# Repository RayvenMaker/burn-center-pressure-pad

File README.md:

# burn-center-pressure-pad
A 128 x 128 pressure sensing matrix designed to work in a hospital setting.

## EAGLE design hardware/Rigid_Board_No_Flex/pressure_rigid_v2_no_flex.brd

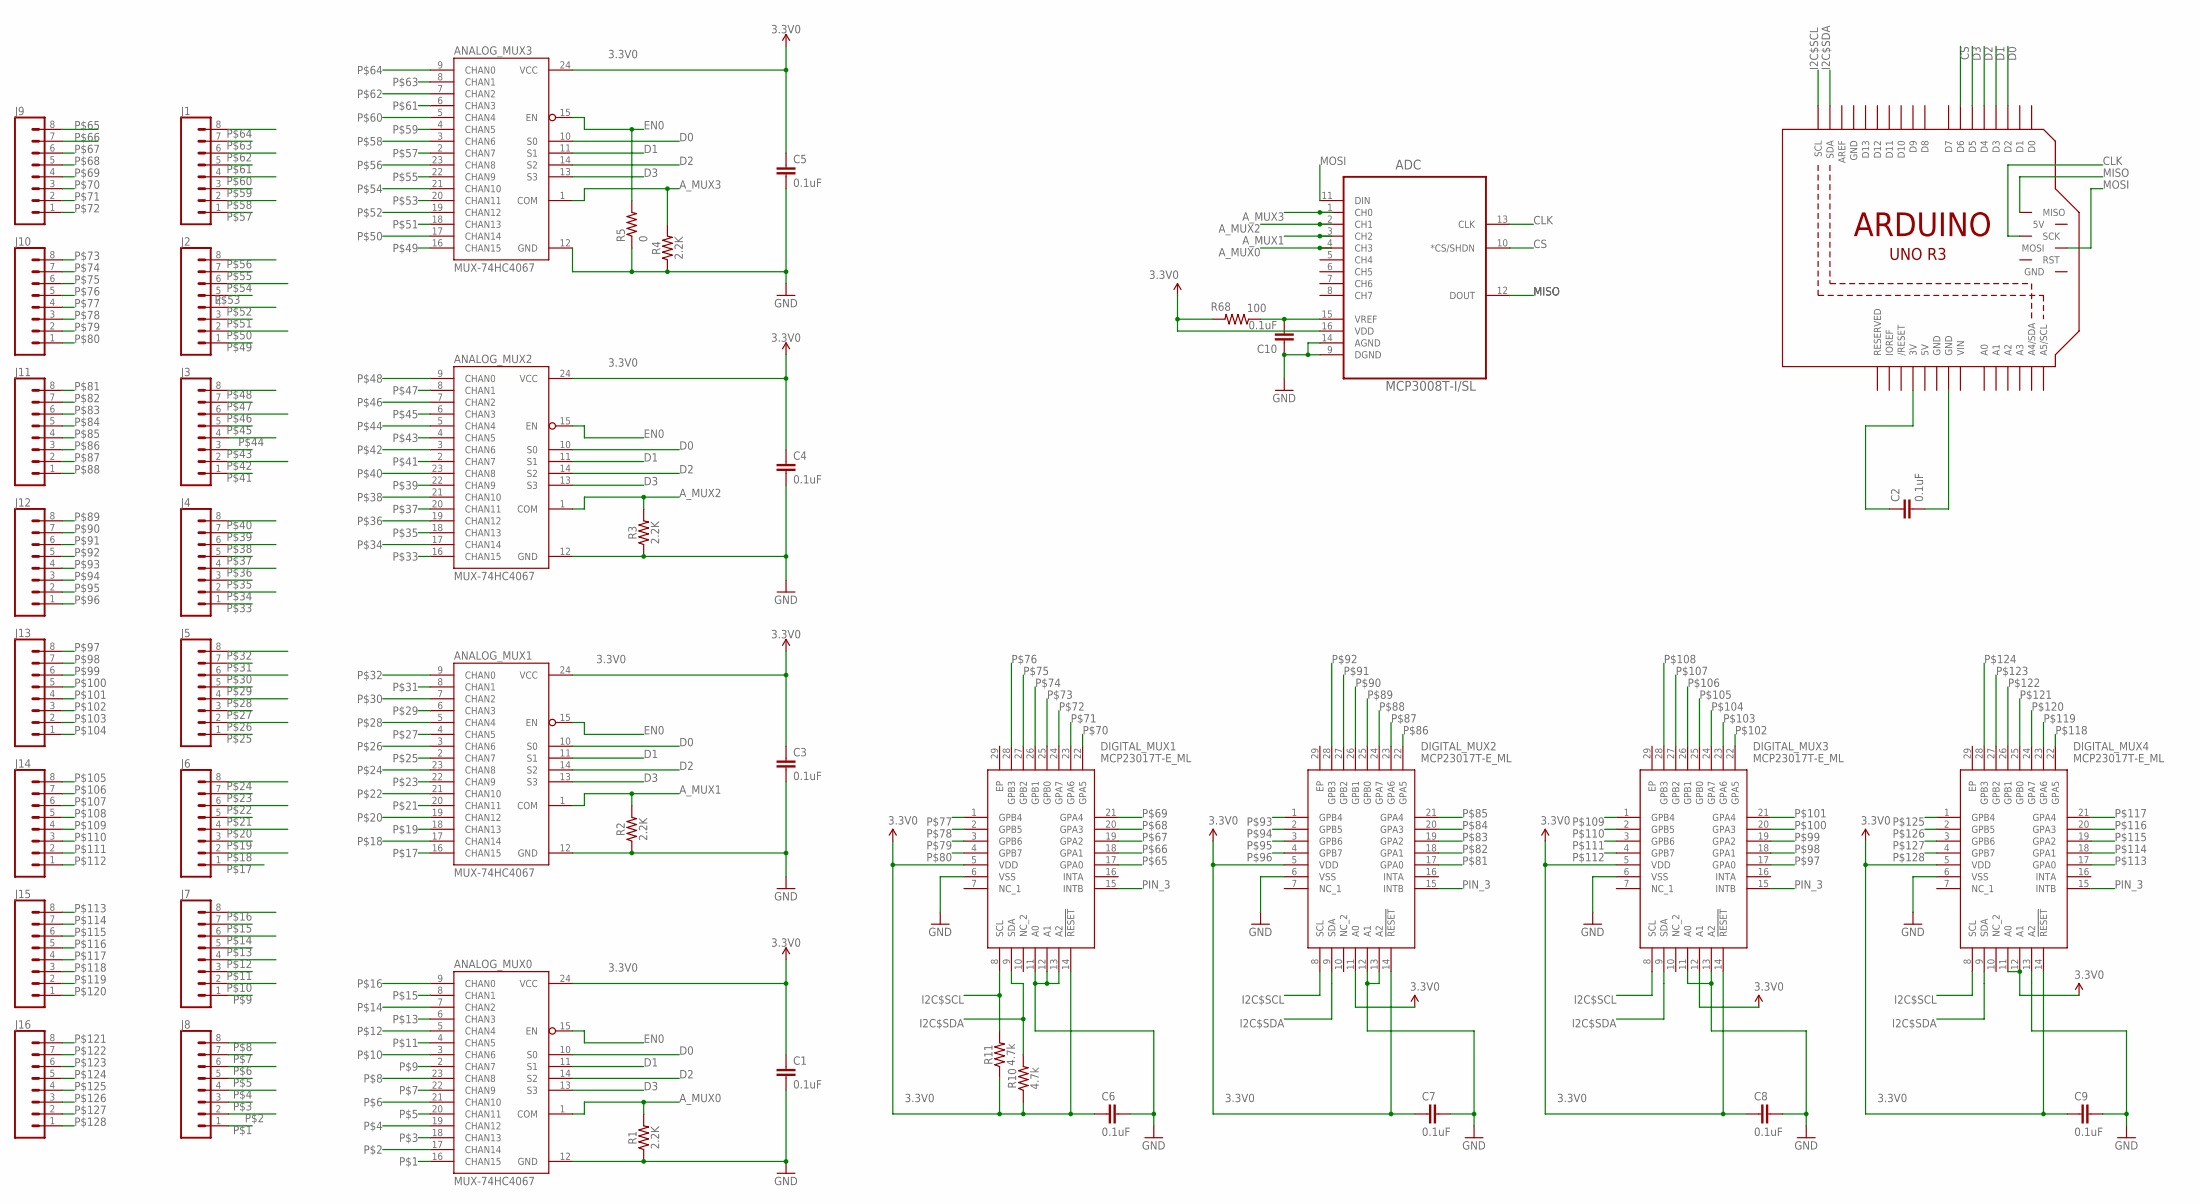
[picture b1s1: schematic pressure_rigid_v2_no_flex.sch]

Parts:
ADC: MCP3008T-I/SL; SOIC127P600X175-16N
ANALOG_MUX0, ANALOG_MUX1, ANALOG_MUX2, ANALOG_MUX3: MUX-74HC4067; SSOP24
C1, C3, C4, C5, C6, C7, C8, C9, C10: 0.1uF; 0402
C2: 0.1uF; 0603
DIGITAL_MUX1, DIGITAL_MUX2, DIGITAL_MUX3, DIGITAL_MUX4: MCP23017T-E_ML; QFN65P600X600X100-29N
J1, J2, J3, J4, J5, J6, J7, J8, J9, J10, J11, J12, J13, J14, J15, J16: CONN_08SMD-STRAIGHT-FEMALE; 1X08_SMD
M1: ARDUINO_R3_ICSP_NODIM; ARDUINOR3_ICSP_NODIM
R1, R2, R3, R4: 2.2K; 0402
R5: 0; 0603
R10, R11: 4.7k; 0603
R68: 100; 0603

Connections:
3.3V0: ANALOG_MUX0.24 (VCC), ANALOG_MUX1.24 (VCC), ANALOG_MUX2.24 (VCC), ANALOG_MUX3.24 (VCC), C1.1, C3.1, C4.1, C5.1, C6.1, C7.1, C8.1, C9.1, DIGITAL_MUX1.5 (VDD), DIGITAL_MUX1.14 (!RESET), DIGITAL_MUX2.5 (VDD), DIGITAL_MUX2.14 (!RESET), DIGITAL_MUX3.5 (VDD), DIGITAL_MUX3.14 (!RESET), DIGITAL_MUX4.5 (VDD), DIGITAL_MUX4.14 (!RESET), R10.1, R11.1
5V: M1.5V
A_MUX0: ADC.4 (CH3), ANALOG_MUX0.1 (COM), R1.2
A_MUX1: ADC.3 (CH2), ANALOG_MUX1.1 (COM), R2.2
A_MUX2: ADC.2 (CH1), ANALOG_MUX2.1 (COM), R3.2
A_MUX3: ADC.1 (CH0), ANALOG_MUX3.1 (COM), R4.2
CLK: ADC.13 (CLK), M1.SCK
CS: ADC.10 (*CS/SHDN), M1.D6
D0: ANALOG_MUX0.10 (S0), ANALOG_MUX1.10 (S0), ANALOG_MUX2.10 (S0), ANALOG_MUX3.10 (S0), M1.D2
D1: ANALOG_MUX0.11 (S1), ANALOG_MUX1.11 (S1), ANALOG_MUX2.11 (S1), ANALOG_MUX3.11 (S1), M1.D3
D2: ANALOG_MUX0.14 (S2), ANALOG_MUX1.14 (S2), ANALOG_MUX2.14 (S2), ANALOG_MUX3.14 (S2), M1.D4
D3: ANALOG_MUX0.13 (S3), ANALOG_MUX1.13 (S3), ANALOG_MUX2.13 (S3), ANALOG_MUX3.13 (S3), M1.D5
EN0: ANALOG_MUX0.15 (EN), ANALOG_MUX1.15 (EN), ANALOG_MUX2.15 (EN), ANALOG_MUX3.15 (EN), R5.2
GND: ADC.9 (DGND), ADC.14 (AGND), ANALOG_MUX0.12 (GND), ANALOG_MUX1.12 (GND), ANALOG_MUX2.12 (GND), ANALOG_MUX3.12 (GND), C1.2, C3.2, C4.2, C5.2, C6.2, C7.2, C8.2, C9.2, C10.1, DIGITAL_MUX1.6 (VSS), DIGITAL_MUX1.11 (A0), DIGITAL_MUX1.12 (A1), DIGITAL_MUX1.13 (A2), DIGITAL_MUX2.6 (VSS), DIGITAL_MUX2.12 (A1), DIGITAL_MUX2.13 (A2), DIGITAL_MUX3.6 (VSS), DIGITAL_MUX3.11 (A0), DIGITAL_MUX3.13 (A2), DIGITAL_MUX4.6 (VSS), DIGITAL_MUX4.13 (A2), M1.GND, M1.GND@1 (GND), R1.1, R2.1, R3.1, R4.1, R5.1
I2C$SCL: DIGITAL_MUX1.8 (SCL), DIGITAL_MUX2.8 (SCL), DIGITAL_MUX3.8 (SCL), DIGITAL_MUX4.8 (SCL), M1.SCL, R11.2
I2C$SDA: DIGITAL_MUX1.9 (SDA), DIGITAL_MUX2.9 (SDA), DIGITAL_MUX3.9 (SDA), DIGITAL_MUX4.9 (SDA), M1.SDA, R10.2
MISO: ADC.12 (DOUT), M1.MISO
MOSI: ADC.11 (DIN), M1.MOSI
unnamed: ADC.15 (VREF), C10.2, R68.1
unnamed: C2.2, M1.GND@3 (GND)
unnamed: C2.1, M1.3V
P$1: ANALOG_MUX0.16 (CHAN15), J8.1
P$2: ANALOG_MUX0.17 (CHAN14), J8.2
P$3: ANALOG_MUX0.18 (CHAN13), J8.3
P$4: ANALOG_MUX0.19 (CHAN12), J8.4
P$5: ANALOG_MUX0.20 (CHAN11), J8.5
P$6: ANALOG_MUX0.21 (CHAN10), J8.6
P$7: ANALOG_MUX0.22 (CHAN9), J8.7
P$8: ANALOG_MUX0.23 (CHAN8), J8.8
P$9: ANALOG_MUX0.2 (CHAN7), J7.1
P$10: ANALOG_MUX0.3 (CHAN6), J7.2
P$11: ANALOG_MUX0.4 (CHAN5), J7.3
P$12: ANALOG_MUX0.5 (CHAN4), J7.4
P$13: ANALOG_MUX0.6 (CHAN3), J7.5
P$14: ANALOG_MUX0.7 (CHAN2), J7.6
P$15: ANALOG_MUX0.8 (CHAN1), J7.7
P$16: ANALOG_MUX0.9 (CHAN0), J7.8
P$17: ANALOG_MUX1.16 (CHAN15), J6.1
P$18: ANALOG_MUX1.17 (CHAN14), J6.2
P$19: ANALOG_MUX1.18 (CHAN13), J6.3
P$20: ANALOG_MUX1.19 (CHAN12), J6.4
P$21: ANALOG_MUX1.20 (CHAN11), J6.5
P$22: ANALOG_MUX1.21 (CHAN10), J6.6
P$23: ANALOG_MUX1.22 (CHAN9), J6.7
P$24: ANALOG_MUX1.23 (CHAN8), J6.8
P$25: ANALOG_MUX1.2 (CHAN7), J5.1
P$26: ANALOG_MUX1.3 (CHAN6), J5.2
P$27: ANALOG_MUX1.4 (CHAN5), J5.3
P$28: ANALOG_MUX1.5 (CHAN4), J5.4
P$29: ANALOG_MUX1.6 (CHAN3), J5.5
P$30: ANALOG_MUX1.7 (CHAN2), J5.6
P$31: ANALOG_MUX1.8 (CHAN1), J5.7
P$32: ANALOG_MUX1.9 (CHAN0), J5.8
P$33: ANALOG_MUX2.16 (CHAN15), J4.1
P$34: ANALOG_MUX2.17 (CHAN14), J4.2
P$35: ANALOG_MUX2.18 (CHAN13), J4.3
P$36: ANALOG_MUX2.19 (CHAN12), J4.4
P$37: ANALOG_MUX2.20 (CHAN11), J4.5
P$38: ANALOG_MUX2.21 (CHAN10), J4.6
P$39: ANALOG_MUX2.22 (CHAN9), J4.7
P$40: ANALOG_MUX2.23 (CHAN8), J4.8
P$41: ANALOG_MUX2.2 (CHAN7), J3.1
P$42: ANALOG_MUX2.3 (CHAN6), J3.2
P$43: ANALOG_MUX2.4 (CHAN5), J3.3
P$44: ANALOG_MUX2.5 (CHAN4), J3.4
P$45: ANALOG_MUX2.6 (CHAN3), J3.5
P$46: ANALOG_MUX2.7 (CHAN2), J3.6
P$47: ANALOG_MUX2.8 (CHAN1), J3.7
P$48: ANALOG_MUX2.9 (CHAN0), J3.8
P$49: ANALOG_MUX3.16 (CHAN15), J2.1
P$50: ANALOG_MUX3.17 (CHAN14), J2.2
P$51: ANALOG_MUX3.18 (CHAN13), J2.3
P$52: ANALOG_MUX3.19 (CHAN12), J2.4
P$53: ANALOG_MUX3.20 (CHAN11), J2.5
P$54: ANALOG_MUX3.21 (CHAN10), J2.6
P$55: ANALOG_MUX3.22 (CHAN9), J2.7
P$56: ANALOG_MUX3.23 (CHAN8), J2.8
P$57: ANALOG_MUX3.2 (CHAN7), J1.1
P$58: ANALOG_MUX3.3 (CHAN6), J1.2
P$59: ANALOG_MUX3.4 (CHAN5), J1.3
P$60: ANALOG_MUX3.5 (CHAN4), J1.4
P$61: ANALOG_MUX3.6 (CHAN3), J1.5
P$62: ANALOG_MUX3.7 (CHAN2), J1.6
P$63: ANALOG_MUX3.8 (CHAN1), J1.7
P$64: ANALOG_MUX3.9 (CHAN0), J1.8
P$65: DIGITAL_MUX1.17 (GPA0), J9.8
P$66: DIGITAL_MUX1.18 (GPA1), J9.7
P$67: DIGITAL_MUX1.19 (GPA2), J9.6
P$68: DIGITAL_MUX1.20 (GPA3), J9.5
P$69: DIGITAL_MUX1.21 (GPA4), J9.4
P$70: DIGITAL_MUX1.22 (GPA5), J9.3
P$71: DIGITAL_MUX1.23 (GPA6), J9.2
P$72: DIGITAL_MUX1.24 (GPA7), J9.1
P$73: DIGITAL_MUX1.25 (GPB0), J10.8
P$74: DIGITAL_MUX1.26 (GPB1), J10.7
P$75: DIGITAL_MUX1.27 (GPB2), J10.6
P$76: DIGITAL_MUX1.28 (GPB3), J10.5
P$77: DIGITAL_MUX1.1 (GPB4), J10.4
P$78: DIGITAL_MUX1.2 (GPB5), J10.3
P$79: DIGITAL_MUX1.3 (GPB6), J10.2
P$80: DIGITAL_MUX1.4 (GPB7), J10.1
P$81: DIGITAL_MUX2.17 (GPA0), J11.8
P$82: DIGITAL_MUX2.18 (GPA1), J11.7
P$83: DIGITAL_MUX2.19 (GPA2), J11.6
P$84: DIGITAL_MUX2.20 (GPA3), J11.5
P$85: DIGITAL_MUX2.21 (GPA4), J11.4
P$86: DIGITAL_MUX2.22 (GPA5), J11.3
P$87: DIGITAL_MUX2.23 (GPA6), J11.2
P$88: DIGITAL_MUX2.24 (GPA7), J11.1
P$89: DIGITAL_MUX2.25 (GPB0), J12.8
P$90: DIGITAL_MUX2.26 (GPB1), J12.7
P$91: DIGITAL_MUX2.27 (GPB2), J12.6
P$92: DIGITAL_MUX2.28 (GPB3), J12.5
P$93: DIGITAL_MUX2.1 (GPB4), J12.4
P$94: DIGITAL_MUX2.2 (GPB5), J12.3
P$95: DIGITAL_MUX2.3 (GPB6), J12.2
P$96: DIGITAL_MUX2.4 (GPB7), J12.1
P$97: DIGITAL_MUX3.17 (GPA0), J13.8
P$98: DIGITAL_MUX3.18 (GPA1), J13.7
P$99: DIGITAL_MUX3.19 (GPA2), J13.6
P$100: DIGITAL_MUX3.20 (GPA3), J13.5
P$101: DIGITAL_MUX3.21 (GPA4), J13.4
P$102: DIGITAL_MUX3.22 (GPA5), J13.3
P$103: DIGITAL_MUX3.23 (GPA6), J13.2
P$104: DIGITAL_MUX3.24 (GPA7), J13.1
P$105: DIGITAL_MUX3.25 (GPB0), J14.8
P$106: DIGITAL_MUX3.26 (GPB1), J14.7
P$107: DIGITAL_MUX3.27 (GPB2), J14.6
P$108: DIGITAL_MUX3.28 (GPB3), J14.5
P$109: DIGITAL_MUX3.1 (GPB4), J14.4
P$110: DIGITAL_MUX3.2 (GPB5), J14.3
P$111: DIGITAL_MUX3.3 (GPB6), J14.2
P$112: DIGITAL_MUX3.4 (GPB7), J14.1
P$113: DIGITAL_MUX4.17 (GPA0), J15.8
P$114: DIGITAL_MUX4.18 (GPA1), J15.7
P$115: DIGITAL_MUX4.19 (GPA2), J15.6
P$116: DIGITAL_MUX4.20 (GPA3), J15.5
P$117: DIGITAL_MUX4.21 (GPA4), J15.4
P$118: DIGITAL_MUX4.22 (GPA5), J15.3
P$119: DIGITAL_MUX4.23 (GPA6), J15.2
P$120: DIGITAL_MUX4.24 (GPA7), J15.1
P$121: DIGITAL_MUX4.25 (GPB0), J16.8
P$122: DIGITAL_MUX4.26 (GPB1), J16.7
P$123: DIGITAL_MUX4.27 (GPB2), J16.6
P$124: DIGITAL_MUX4.28 (GPB3), J16.5
P$125: DIGITAL_MUX4.1 (GPB4), J16.4
P$126: DIGITAL_MUX4.2 (GPB5), J16.3
P$127: DIGITAL_MUX4.3 (GPB6), J16.2
P$128: DIGITAL_MUX4.4 (GPB7), J16.1
PIN_3: DIGITAL_MUX1.15 (INTB), DIGITAL_MUX2.15 (INTB), DIGITAL_MUX3.15 (INTB), DIGITAL_MUX4.15 (INTB)
VCC: ADC.16 (VDD), DIGITAL_MUX2.11 (A0), DIGITAL_MUX3.12 (A1), DIGITAL_MUX4.11 (A0), DIGITAL_MUX4.12 (A1), R68.2
VIN: M1.VIN

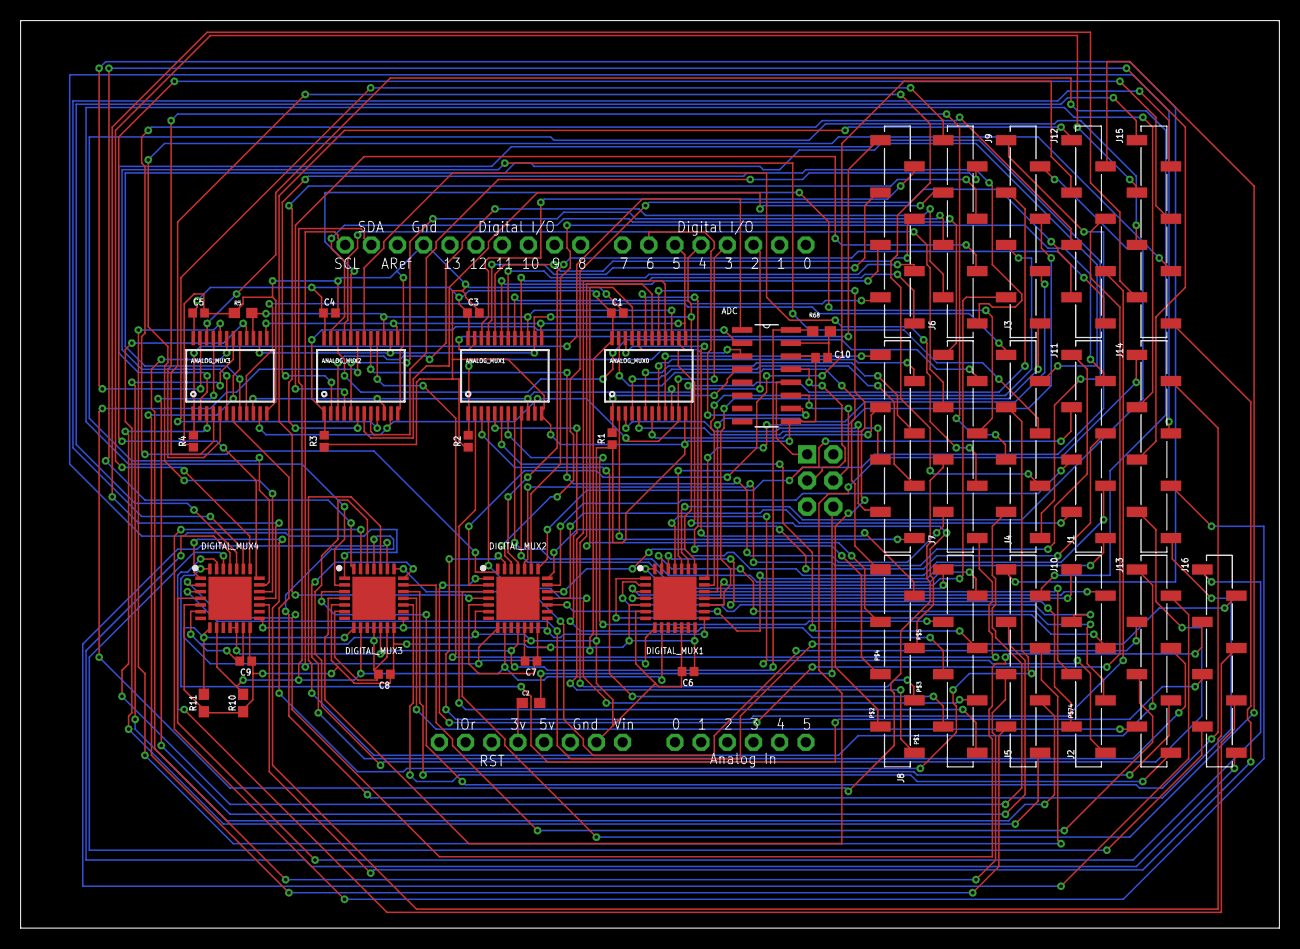
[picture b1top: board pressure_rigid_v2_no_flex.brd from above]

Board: 2 copper layers, 122.2 x 88.1 mm, 44 parts (0 on the bottom side), 150 nets.

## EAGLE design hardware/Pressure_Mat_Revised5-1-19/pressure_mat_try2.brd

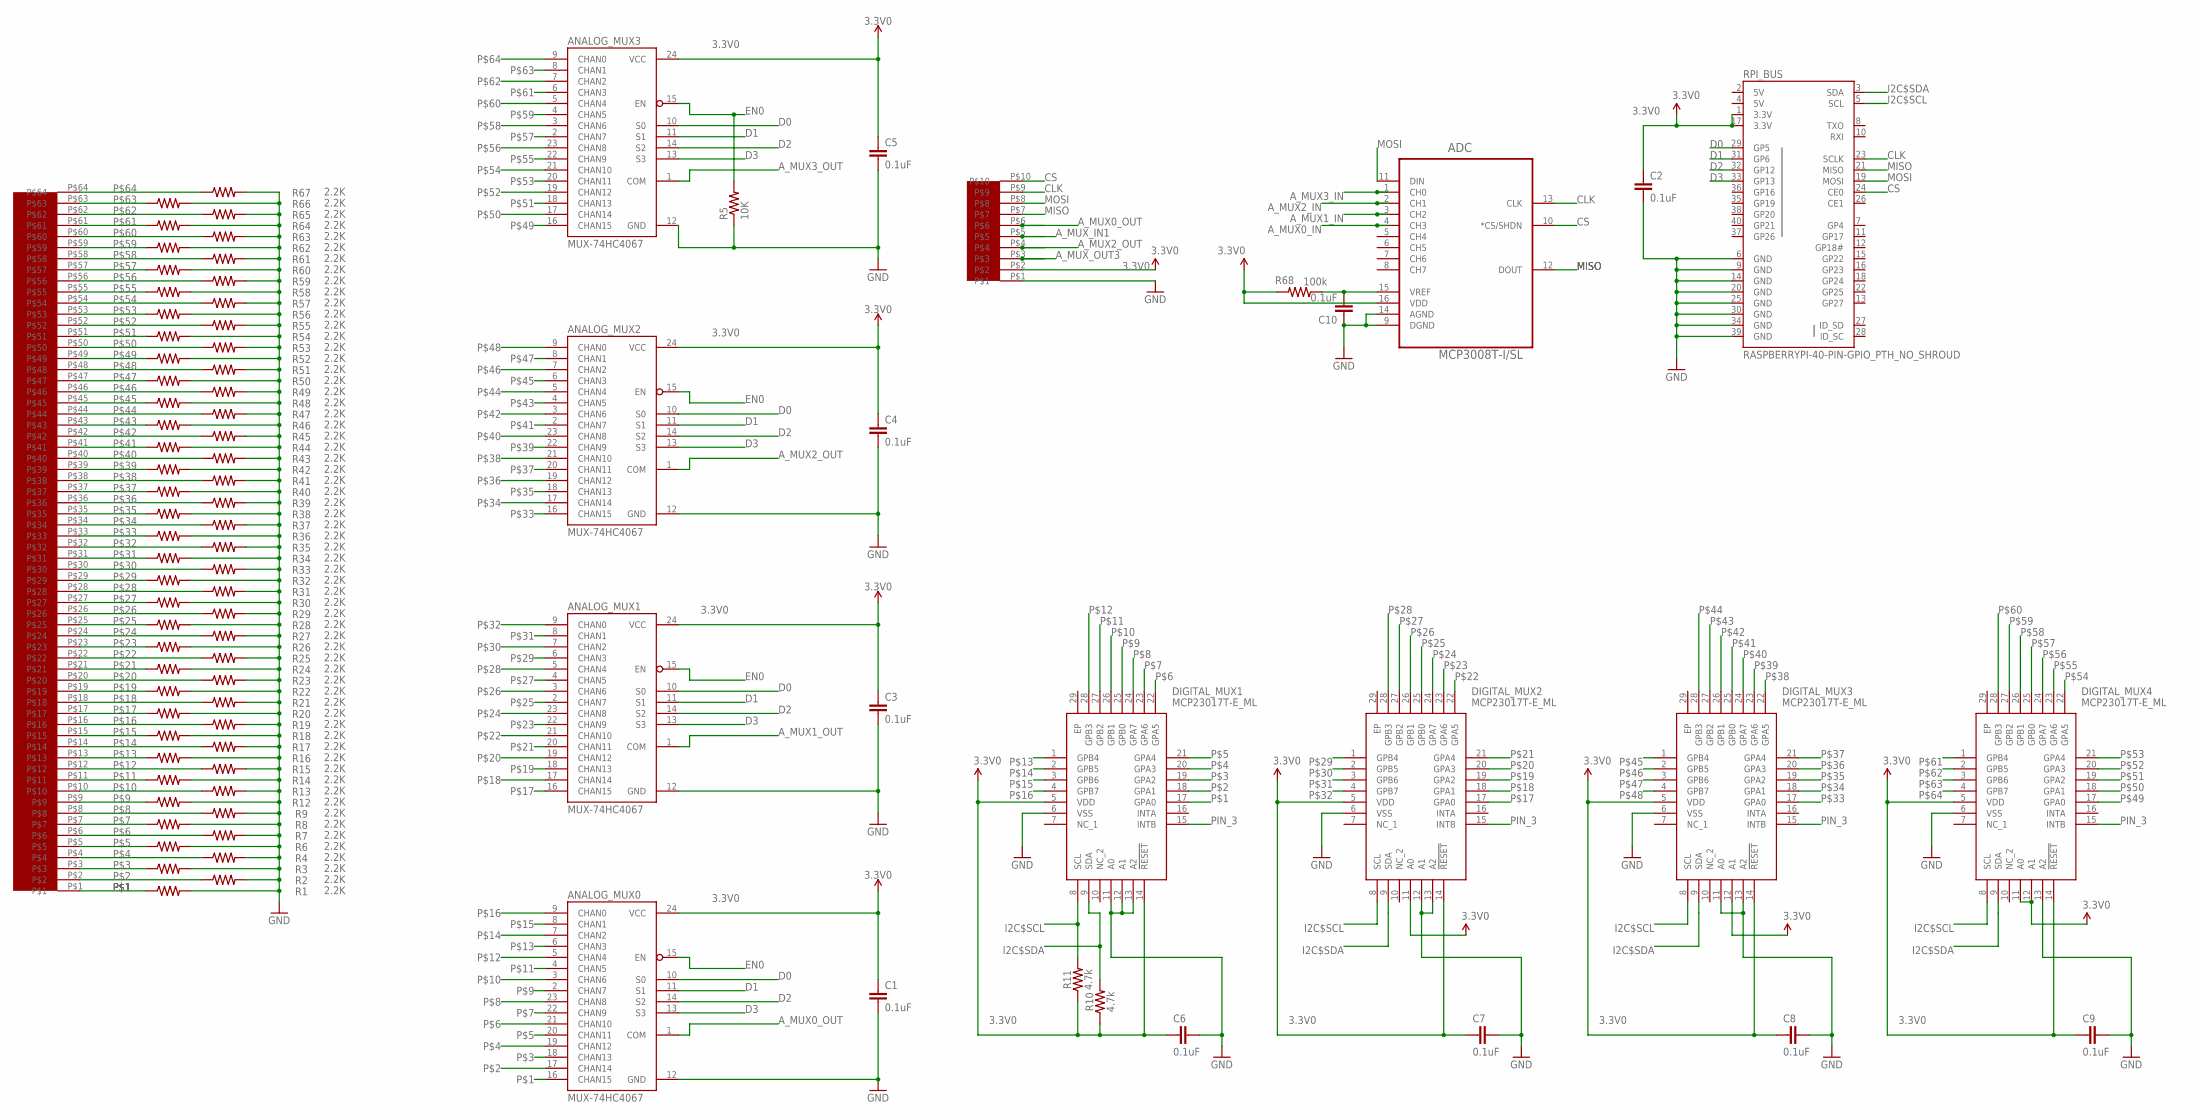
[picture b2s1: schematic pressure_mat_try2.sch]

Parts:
ADC: MCP3008T-I/SL; SOIC127P600X175-16N
ANALOG_MUX0, ANALOG_MUX1, ANALOG_MUX2, ANALOG_MUX3: MUX-74HC4067; SSOP24
C1, C3, C4, C5, C6, C7, C8, C9, C10: 0.1uF; 0402
C2: 0.1uF; 0603
DIGITAL_MUX1, DIGITAL_MUX2, DIGITAL_MUX3, DIGITAL_MUX4: MCP23017T-E_ML; QFN65P600X600X100-29N
PAD_BUS: PCB_CONNECTOR_10_PIN
R1, R2, R3, R4, R6, R7, R8, R9, R12, R13, R14, R15, R16, R17, R18, R19, R20, R21, R22, R23, R24, R25, R26, R27, R28, R29, R30, R31, R32, R33, R34, R35, R36, R37, R38, R39, R40, R41, R42, R43, R44, R45, R46, R47, R48, R49, R50, R51, R52, R53, R54, R55, R56, R57, R58, R59, R60, R61, R62, R63, R64, R65, R66, R67: 2.2K; 0402
R5: 10K; 0603
R10, R11: 4.7k; 0603
R68: 100k; 0603
RPI_BUS: RASPBERRYPI-40-PIN-GPIO_PTH_NO_SHROUD; 2X20
U$1: 64GRID

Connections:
3.3V0: ANALOG_MUX0.24 (VCC), ANALOG_MUX1.24 (VCC), ANALOG_MUX2.24 (VCC), ANALOG_MUX3.24 (VCC), C1.1, C2.1, C3.1, C4.1, C5.1, C6.1, C7.1, C8.1, C9.1, DIGITAL_MUX1.5 (VDD), DIGITAL_MUX1.14 (!RESET), DIGITAL_MUX2.5 (VDD), DIGITAL_MUX2.14 (!RESET), DIGITAL_MUX3.5 (VDD), DIGITAL_MUX3.14 (!RESET), DIGITAL_MUX4.5 (VDD), DIGITAL_MUX4.14 (!RESET), PAD_BUS.P$2, R10.1, R11.1, RPI_BUS.1 (3.3V), RPI_BUS.17 (3.3V)
5V: RPI_BUS.2 (5V), RPI_BUS.4 (5V)
A_MUX0_IN: ADC.4 (CH3)
A_MUX0_OUT: ANALOG_MUX0.1 (COM), PAD_BUS.P$6
A_MUX1_IN: ADC.3 (CH2)
A_MUX1_OUT: ANALOG_MUX1.1 (COM)
A_MUX2_IN: ADC.2 (CH1)
A_MUX2_OUT: ANALOG_MUX2.1 (COM), PAD_BUS.P$4
A_MUX3_IN: ADC.1 (CH0)
A_MUX3_OUT: ANALOG_MUX3.1 (COM)
A_MUX_IN1: PAD_BUS.P$5
A_MUX_OUT3: PAD_BUS.P$3
CLK: ADC.13 (CLK), PAD_BUS.P$9, RPI_BUS.23 (SCLK)
CS: ADC.10 (*CS/SHDN), PAD_BUS.P$10, RPI_BUS.24 (CE0)
D0: ANALOG_MUX0.10 (S0), ANALOG_MUX1.10 (S0), ANALOG_MUX2.10 (S0), ANALOG_MUX3.10 (S0), RPI_BUS.29 (GP5)
D1: ANALOG_MUX0.11 (S1), ANALOG_MUX1.11 (S1), ANALOG_MUX2.11 (S1), ANALOG_MUX3.11 (S1), RPI_BUS.31 (GP6)
D2: ANALOG_MUX0.14 (S2), ANALOG_MUX1.14 (S2), ANALOG_MUX2.14 (S2), ANALOG_MUX3.14 (S2), RPI_BUS.32 (GP12)
D3: ANALOG_MUX0.13 (S3), ANALOG_MUX1.13 (S3), ANALOG_MUX2.13 (S3), ANALOG_MUX3.13 (S3), RPI_BUS.33 (GP13)
EN0: ANALOG_MUX0.15 (EN), ANALOG_MUX1.15 (EN), ANALOG_MUX2.15 (EN), ANALOG_MUX3.15 (EN), R5.2
GND: ADC.9 (DGND), ADC.14 (AGND), ANALOG_MUX0.12 (GND), ANALOG_MUX1.12 (GND), ANALOG_MUX2.12 (GND), ANALOG_MUX3.12 (GND), C1.2, C2.2, C3.2, C4.2, C5.2, C6.2, C7.2, C8.2, C9.2, C10.1, DIGITAL_MUX1.6 (VSS), DIGITAL_MUX1.11 (A0), DIGITAL_MUX1.12 (A1), DIGITAL_MUX1.13 (A2), DIGITAL_MUX2.6 (VSS), DIGITAL_MUX2.12 (A1), DIGITAL_MUX2.13 (A2), DIGITAL_MUX3.6 (VSS), DIGITAL_MUX3.11 (A0), DIGITAL_MUX3.13 (A2), DIGITAL_MUX4.6 (VSS), DIGITAL_MUX4.13 (A2), PAD_BUS.P$1, R1.2, R2.2, R3.2, R4.2, R5.1, R6.2, R7.2, R8.2, R9.2, R12.2, R13.2, R14.2, R15.2, R16.2, R17.2, R18.2, R19.2, R20.2, R21.2, R22.2, R23.2, R24.2, R25.2, R26.2, R27.2, R28.2, R29.2, R30.2, R31.2, R32.2, R33.2, R34.2, R35.2, R36.2, R37.2, R38.2, R39.2, R40.2, R41.2, R42.2, R43.2, R44.2, R45.2, R46.2, R47.2, R48.2, R49.2, R50.2, R51.2, R52.2, R53.2, R54.2, R55.2, R56.2, R57.2, R58.2, R59.2, R60.2, R61.2, R62.2, R63.2, R64.2, R65.2, R66.2, R67.2, RPI_BUS.6 (GND), RPI_BUS.9 (GND), RPI_BUS.14 (GND), RPI_BUS.20 (GND), RPI_BUS.25 (GND), RPI_BUS.30 (GND), RPI_BUS.34 (GND), RPI_BUS.39 (GND)
I2C$SCL: DIGITAL_MUX1.8 (SCL), DIGITAL_MUX2.8 (SCL), DIGITAL_MUX3.8 (SCL), DIGITAL_MUX4.8 (SCL), R11.2, RPI_BUS.5 (SCL)
I2C$SDA: DIGITAL_MUX1.9 (SDA), DIGITAL_MUX2.9 (SDA), DIGITAL_MUX3.9 (SDA), DIGITAL_MUX4.9 (SDA), R10.2, RPI_BUS.3 (SDA)
MISO: ADC.12 (DOUT), PAD_BUS.P$7, RPI_BUS.21 (MISO)
MOSI: ADC.11 (DIN), PAD_BUS.P$8, RPI_BUS.19 (MOSI)
unnamed: ADC.15 (VREF), C10.2, R68.1
P$1: ANALOG_MUX0.16 (CHAN15), DIGITAL_MUX1.17 (GPA0), R1.1, U$1.P$1
P$2: ANALOG_MUX0.17 (CHAN14), DIGITAL_MUX1.18 (GPA1), R2.1, U$1.P$2
P$3: ANALOG_MUX0.18 (CHAN13), DIGITAL_MUX1.19 (GPA2), R3.1, U$1.P$3
P$4: ANALOG_MUX0.19 (CHAN12), DIGITAL_MUX1.20 (GPA3), R4.1, U$1.P$4
P$5: ANALOG_MUX0.20 (CHAN11), DIGITAL_MUX1.21 (GPA4), R6.1, U$1.P$5
P$6: ANALOG_MUX0.21 (CHAN10), DIGITAL_MUX1.22 (GPA5), R7.1, U$1.P$6
P$7: ANALOG_MUX0.22 (CHAN9), DIGITAL_MUX1.23 (GPA6), R8.1, U$1.P$7
P$8: ANALOG_MUX0.23 (CHAN8), DIGITAL_MUX1.24 (GPA7), R9.1, U$1.P$8
P$9: ANALOG_MUX0.2 (CHAN7), DIGITAL_MUX1.25 (GPB0), R12.1, U$1.P$9
P$10: ANALOG_MUX0.3 (CHAN6), DIGITAL_MUX1.26 (GPB1), R13.1, U$1.P$10
P$11: ANALOG_MUX0.4 (CHAN5), DIGITAL_MUX1.27 (GPB2), R14.1, U$1.P$11
P$12: ANALOG_MUX0.5 (CHAN4), DIGITAL_MUX1.28 (GPB3), R15.1, U$1.P$12
P$13: ANALOG_MUX0.6 (CHAN3), DIGITAL_MUX1.1 (GPB4), R16.1, U$1.P$13
P$14: ANALOG_MUX0.7 (CHAN2), DIGITAL_MUX1.2 (GPB5), R17.1, U$1.P$14
P$15: ANALOG_MUX0.8 (CHAN1), DIGITAL_MUX1.3 (GPB6), R18.1, U$1.P$15
P$16: ANALOG_MUX0.9 (CHAN0), DIGITAL_MUX1.4 (GPB7), R19.1, U$1.P$16
P$17: ANALOG_MUX1.16 (CHAN15), DIGITAL_MUX2.17 (GPA0), R20.1, U$1.P$17
P$18: ANALOG_MUX1.17 (CHAN14), DIGITAL_MUX2.18 (GPA1), R21.1, U$1.P$18
P$19: ANALOG_MUX1.18 (CHAN13), DIGITAL_MUX2.19 (GPA2), R22.1, U$1.P$19
P$20: ANALOG_MUX1.19 (CHAN12), DIGITAL_MUX2.20 (GPA3), R23.1, U$1.P$20
P$21: ANALOG_MUX1.20 (CHAN11), DIGITAL_MUX2.21 (GPA4), R24.1, U$1.P$21
P$22: ANALOG_MUX1.21 (CHAN10), DIGITAL_MUX2.22 (GPA5), R25.1, U$1.P$22
P$23: ANALOG_MUX1.22 (CHAN9), DIGITAL_MUX2.23 (GPA6), R26.1, U$1.P$23
P$24: ANALOG_MUX1.23 (CHAN8), DIGITAL_MUX2.24 (GPA7), R27.1, U$1.P$24
P$25: ANALOG_MUX1.2 (CHAN7), DIGITAL_MUX2.25 (GPB0), R28.1, U$1.P$25
P$26: ANALOG_MUX1.3 (CHAN6), DIGITAL_MUX2.26 (GPB1), R29.1, U$1.P$26
P$27: ANALOG_MUX1.4 (CHAN5), DIGITAL_MUX2.27 (GPB2), R30.1, U$1.P$27
P$28: ANALOG_MUX1.5 (CHAN4), DIGITAL_MUX2.28 (GPB3), R31.1, U$1.P$28
P$29: ANALOG_MUX1.6 (CHAN3), DIGITAL_MUX2.1 (GPB4), R32.1, U$1.P$29
P$30: ANALOG_MUX1.7 (CHAN2), DIGITAL_MUX2.2 (GPB5), R33.1, U$1.P$30
P$31: ANALOG_MUX1.8 (CHAN1), DIGITAL_MUX2.3 (GPB6), R34.1, U$1.P$31
P$32: ANALOG_MUX1.9 (CHAN0), DIGITAL_MUX2.4 (GPB7), R35.1, U$1.P$32
P$33: ANALOG_MUX2.16 (CHAN15), DIGITAL_MUX3.17 (GPA0), R36.1, U$1.P$33
P$34: ANALOG_MUX2.17 (CHAN14), DIGITAL_MUX3.18 (GPA1), R37.1, U$1.P$34
P$35: ANALOG_MUX2.18 (CHAN13), DIGITAL_MUX3.19 (GPA2), R38.1, U$1.P$35
P$36: ANALOG_MUX2.19 (CHAN12), DIGITAL_MUX3.20 (GPA3), R39.1, U$1.P$36
P$37: ANALOG_MUX2.20 (CHAN11), DIGITAL_MUX3.21 (GPA4), R40.1, U$1.P$37
P$38: ANALOG_MUX2.21 (CHAN10), DIGITAL_MUX3.22 (GPA5), R41.1, U$1.P$38
P$39: ANALOG_MUX2.22 (CHAN9), DIGITAL_MUX3.23 (GPA6), R42.1, U$1.P$39
P$40: ANALOG_MUX2.23 (CHAN8), DIGITAL_MUX3.24 (GPA7), R43.1, U$1.P$40
P$41: ANALOG_MUX2.2 (CHAN7), DIGITAL_MUX3.25 (GPB0), R44.1, U$1.P$41
P$42: ANALOG_MUX2.3 (CHAN6), DIGITAL_MUX3.26 (GPB1), R45.1, U$1.P$42
P$43: ANALOG_MUX2.4 (CHAN5), DIGITAL_MUX3.27 (GPB2), R46.1, U$1.P$43
P$44: ANALOG_MUX2.5 (CHAN4), DIGITAL_MUX3.28 (GPB3), R47.1, U$1.P$44
P$45: ANALOG_MUX2.6 (CHAN3), DIGITAL_MUX3.1 (GPB4), R48.1, U$1.P$45
P$46: ANALOG_MUX2.7 (CHAN2), DIGITAL_MUX3.2 (GPB5), R49.1, U$1.P$46
P$47: ANALOG_MUX2.8 (CHAN1), DIGITAL_MUX3.3 (GPB6), R50.1, U$1.P$47
P$48: ANALOG_MUX2.9 (CHAN0), DIGITAL_MUX3.4 (GPB7), R51.1, U$1.P$48
P$49: ANALOG_MUX3.16 (CHAN15), DIGITAL_MUX4.17 (GPA0), R52.1, U$1.P$49
P$50: ANALOG_MUX3.17 (CHAN14), DIGITAL_MUX4.18 (GPA1), R53.1, U$1.P$50
P$51: ANALOG_MUX3.18 (CHAN13), DIGITAL_MUX4.19 (GPA2), R54.1, U$1.P$51
P$52: ANALOG_MUX3.19 (CHAN12), DIGITAL_MUX4.20 (GPA3), R55.1, U$1.P$52
P$53: ANALOG_MUX3.20 (CHAN11), DIGITAL_MUX4.21 (GPA4), R56.1, U$1.P$53
P$54: ANALOG_MUX3.21 (CHAN10), DIGITAL_MUX4.22 (GPA5), R57.1, U$1.P$54
P$55: ANALOG_MUX3.22 (CHAN9), DIGITAL_MUX4.23 (GPA6), R58.1, U$1.P$55
P$56: ANALOG_MUX3.23 (CHAN8), DIGITAL_MUX4.24 (GPA7), R59.1, U$1.P$56
P$57: ANALOG_MUX3.2 (CHAN7), DIGITAL_MUX4.25 (GPB0), R60.1, U$1.P$57
P$58: ANALOG_MUX3.3 (CHAN6), DIGITAL_MUX4.26 (GPB1), R61.1, U$1.P$58
P$59: ANALOG_MUX3.4 (CHAN5), DIGITAL_MUX4.27 (GPB2), R62.1, U$1.P$59
P$60: ANALOG_MUX3.5 (CHAN4), DIGITAL_MUX4.28 (GPB3), R63.1, U$1.P$60
P$61: ANALOG_MUX3.6 (CHAN3), DIGITAL_MUX4.1 (GPB4), R64.1, U$1.P$61
P$62: ANALOG_MUX3.7 (CHAN2), DIGITAL_MUX4.2 (GPB5), R65.1, U$1.P$62
P$63: ANALOG_MUX3.8 (CHAN1), DIGITAL_MUX4.3 (GPB6), R66.1, U$1.P$63
P$64: ANALOG_MUX3.9 (CHAN0), DIGITAL_MUX4.4 (GPB7), R67.1, U$1.P$64
PIN_3: DIGITAL_MUX1.15 (INTB), DIGITAL_MUX2.15 (INTB), DIGITAL_MUX3.15 (INTB), DIGITAL_MUX4.15 (INTB)
VCC: ADC.16 (VDD), DIGITAL_MUX2.11 (A0), DIGITAL_MUX3.12 (A1), DIGITAL_MUX4.11 (A0), DIGITAL_MUX4.12 (A1), R68.2

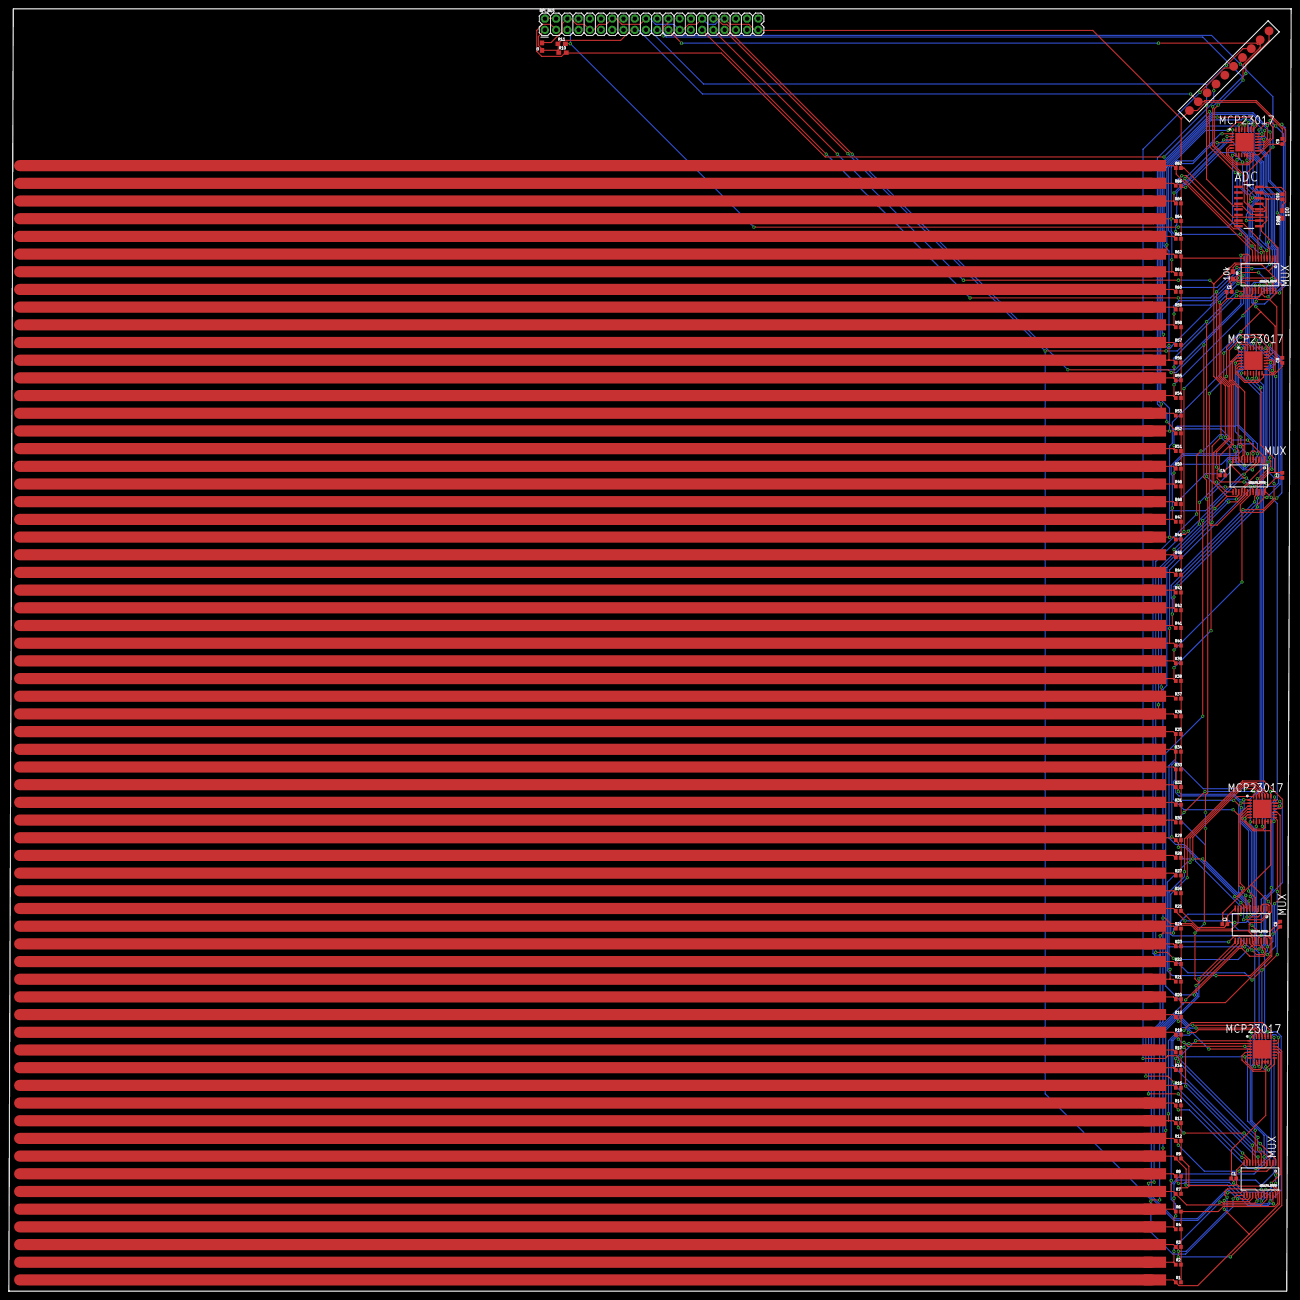
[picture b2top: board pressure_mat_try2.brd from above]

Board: 2 copper layers, 290.0 x 290.0 mm, 90 parts (0 on the bottom side), 83 nets.

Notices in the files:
parts and their libraries:
SparkFun-Boards: Licensing: Creative Commons ShareAlike 4.0 International - https://creativecommons.org/licenses/by-sa/4.0
SparkFun-Aesthetics: Licensing: CC v3.0 Share-Alike You are welcome to use this library for commercial purposes.
SparkFun-Aesthetics: Released under the Creative Commons
